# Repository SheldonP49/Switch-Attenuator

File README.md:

Created in Kicad V6
#
RF Step Attenuator: Adjustable Attenuation Gives Precise Signal Levels.
#
Switch Attenuator, 
When dealing with radio-frequency signals, it often comes in handy to have an easy way to attenuate a signal level in discrete steps. For example, you might want to reduce the output of an RF generator to a lower level than the output control on the generator allows, and there are many other applications of attenuators in the adjustment and repair of receivers and other radio equipment.
#
Schematics and PCB have ben converted from Eagle format and needs final checkes carried out before putting into production.

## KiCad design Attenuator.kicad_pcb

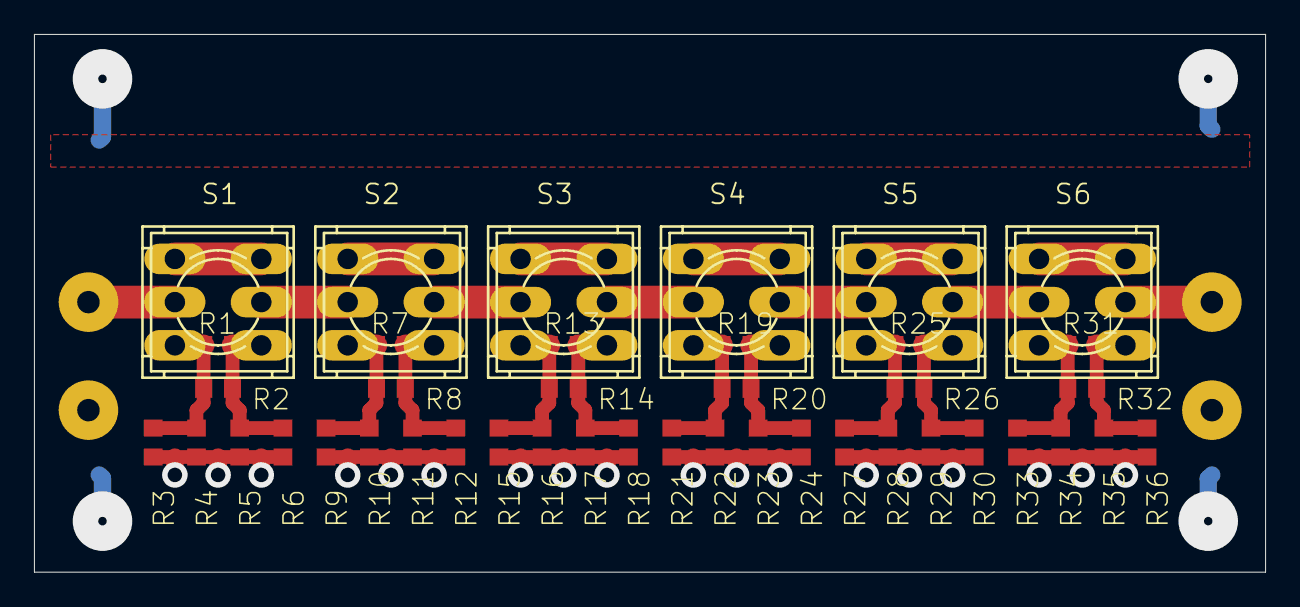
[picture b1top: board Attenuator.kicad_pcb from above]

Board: 2 copper layers, 72.4 x 31.6 mm, 46 parts (0 on the bottom side), 26 nets.

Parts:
R1: 13.7; R0603
R2: 10; R0603
R3, R6: 6810; R0603
R4, R5: 1000; R0603
R7: 316; R0603
R8: 12.1; R0603
R9, R12: 8250; R0603
R10, R11: 464; R0603
R13, R16, R17: 261; R0603
R14: 26.1; R0603
R15, R18: 1470; R0603
R19, R25, R31: 825; R0603
R20, R26, R32: 56.2; R0603
R21, R24, R27, R30, R33, R36: 3160; R0603
R22, R23, R28, R29, R34, R35: 121; R0603
S1, S2, S3, S4, S5, S6: 9077-2
TP1, TP2, TP3, TP4: SE13

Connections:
GND: R3.1, R4.1, R5.1, R6.1, R9.1, R10.1, R11.1, R12.1, R15.1, R16.1, R17.1, R18.1, R21.1, R22.1, R23.1, R24.1, R27.1, R28.1, R29.1, R30.1, R33.1, R34.1, R35.1, R36.1, TP2.MP, TP4.MP
unnamed: R1.1, R2.1, R3.2, R4.2, S1.1
unnamed: R1.2, R2.2, R5.2, R6.2, S1.4
unnamed: R19.1, R20.1, R21.2, R22.2, S4.1
unnamed: S1.3, S1.6
unnamed: S2.3, S2.6
unnamed: R7.1, R8.1, R9.2, R10.2, S2.1
unnamed: R7.2, R8.2, R11.2, R12.2, S2.4
unnamed: S3.3, S3.6
unnamed: S4.3, S4.6
unnamed: R13.1, R14.1, R15.2, R16.2, S3.1
unnamed: R13.2, R14.2, R17.2, R18.2, S3.4
unnamed: S5.3, S5.6
unnamed: S6.3, S6.6
unnamed: R19.2, R20.2, R23.2, R24.2, S4.4
unnamed: S1.5, S2.2
unnamed: S2.5, S3.2
unnamed: R25.1, R26.1, R27.2, R28.2, S5.1
unnamed: R25.2, R26.2, R29.2, R30.2, S5.4
unnamed: S5.5, S6.2
unnamed: S4.5, S5.2
unnamed: R31.1, R32.1, R33.2, R34.2, S6.1
unnamed: R31.2, R32.2, R35.2, R36.2, S6.4
unnamed: S3.5, S4.2
unnamed: S1.2, TP1.MP
unnamed: S6.5, TP3.MP

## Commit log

2023-07-14 tch Attenuator Initial commit following conversion from Eagle Files Raw imporyed Data
2023-07-14 Initial Commit of raw datta following eagle conversion Untested
2023-07-14 Create README.md
    Readme File
